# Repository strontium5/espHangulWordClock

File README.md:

# espHangulWordClock
esp8266 Hangul Word Clock

16x16 = 256 LEDs
2V@20mA
256*0.02 = 5.12A
5.12A*2V = 10.24W

5V@2A = 10W

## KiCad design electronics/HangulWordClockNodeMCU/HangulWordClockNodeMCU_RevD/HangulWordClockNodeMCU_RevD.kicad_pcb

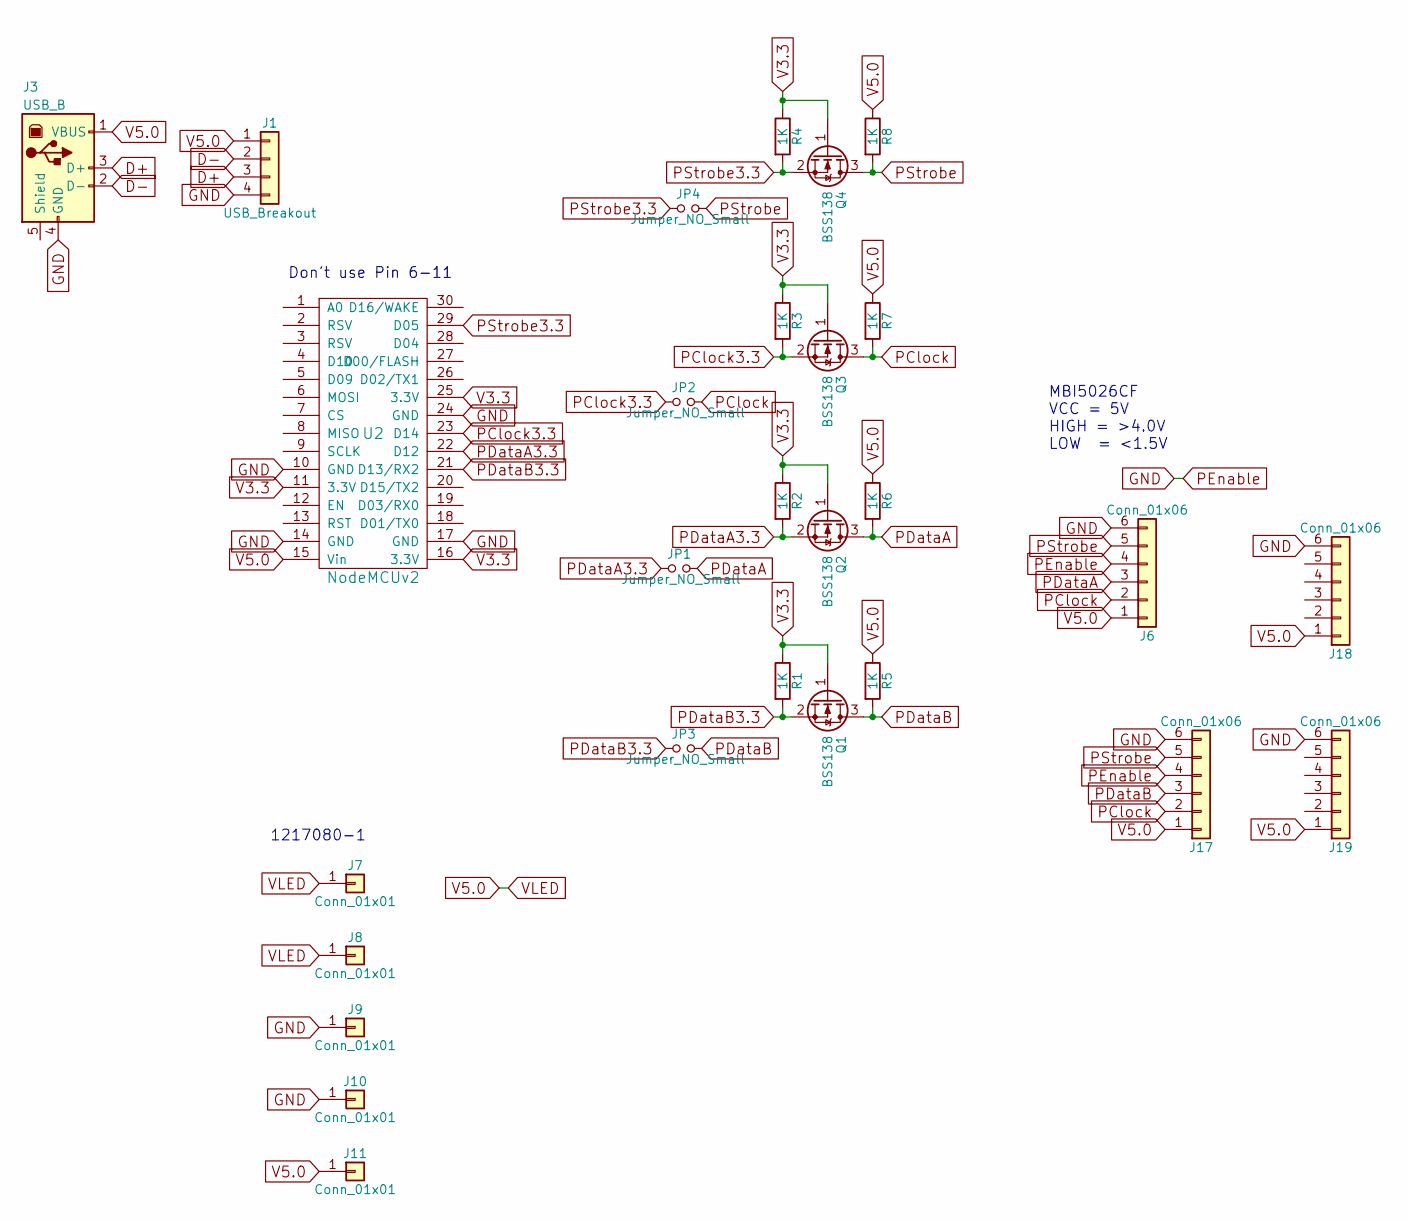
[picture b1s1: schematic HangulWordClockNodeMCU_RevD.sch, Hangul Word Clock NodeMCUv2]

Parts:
J1: USB_Breakout; Pin_Header_Straight_1x04
J3: USB_B
J6, J17, J18, J19: Conn_01x06; Socket_Strip_Straight_1x06
J7, J8, J9, J10, J11: Conn_01x01; 1217080-1
JP1, JP2, JP3, JP4: Jumper_NO_Small; GS2
Q1, Q2, Q3, Q4: BSS138; SOT-23
R1, R2, R3, R4, R5, R6, R7, R8: 1K; R_1206
U2: NodeMCUv2; NodeMCU_V1.0

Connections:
D+: J1.3, J3.3 (D+)
D-: J1.2, J3.2 (D-)
GND: J1.4, J3.4 (GND), J6.4, J6.6, J9.1, J10.1, J17.4, J17.6, J18.6, J19.6, U2.10 (GND), U2.14 (GND), U2.17 (GND), U2.24 (GND)
PClock: J6.2, J17.2, JP2.2, Q3.3 (D), R7.2
PClock3.3: JP2.1, Q3.2 (S), R3.2, U2.23 (D14)
PDataA: J6.3, JP1.2, Q2.3 (D), R6.2
PDataA3.3: JP1.1, Q2.2 (S), R2.2, U2.22 (D12)
PDataB: J17.3, JP3.2, Q1.3 (D), R5.2
PDataB3.3: JP3.1, Q1.2 (S), R1.2, U2.21 (D13/RX2)
PStrobe: J6.5, J17.5, JP4.2, Q4.3 (D), R8.2
PStrobe3.3: JP4.1, Q4.2 (S), R4.2, U2.29 (D05)
V3.3: Q1.1 (G), Q2.1 (G), Q3.1 (G), Q4.1 (G), R1.1, R2.1, R3.1, R4.1, U2.11 (3.3V), U2.16 (3.3V), U2.25 (3.3V)
V5.0: J1.1, J3.1 (VBUS), J6.1, J7.1, J8.1, J11.1, J17.1, J18.1, J19.1, R5.1, R6.1, R7.1, R8.1, U2.15 (Vin)

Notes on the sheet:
MBI5026CF VCC = 5V HIGH = >4.0V LOW = <1.5V
Don't use Pin 6-11
1217080-1

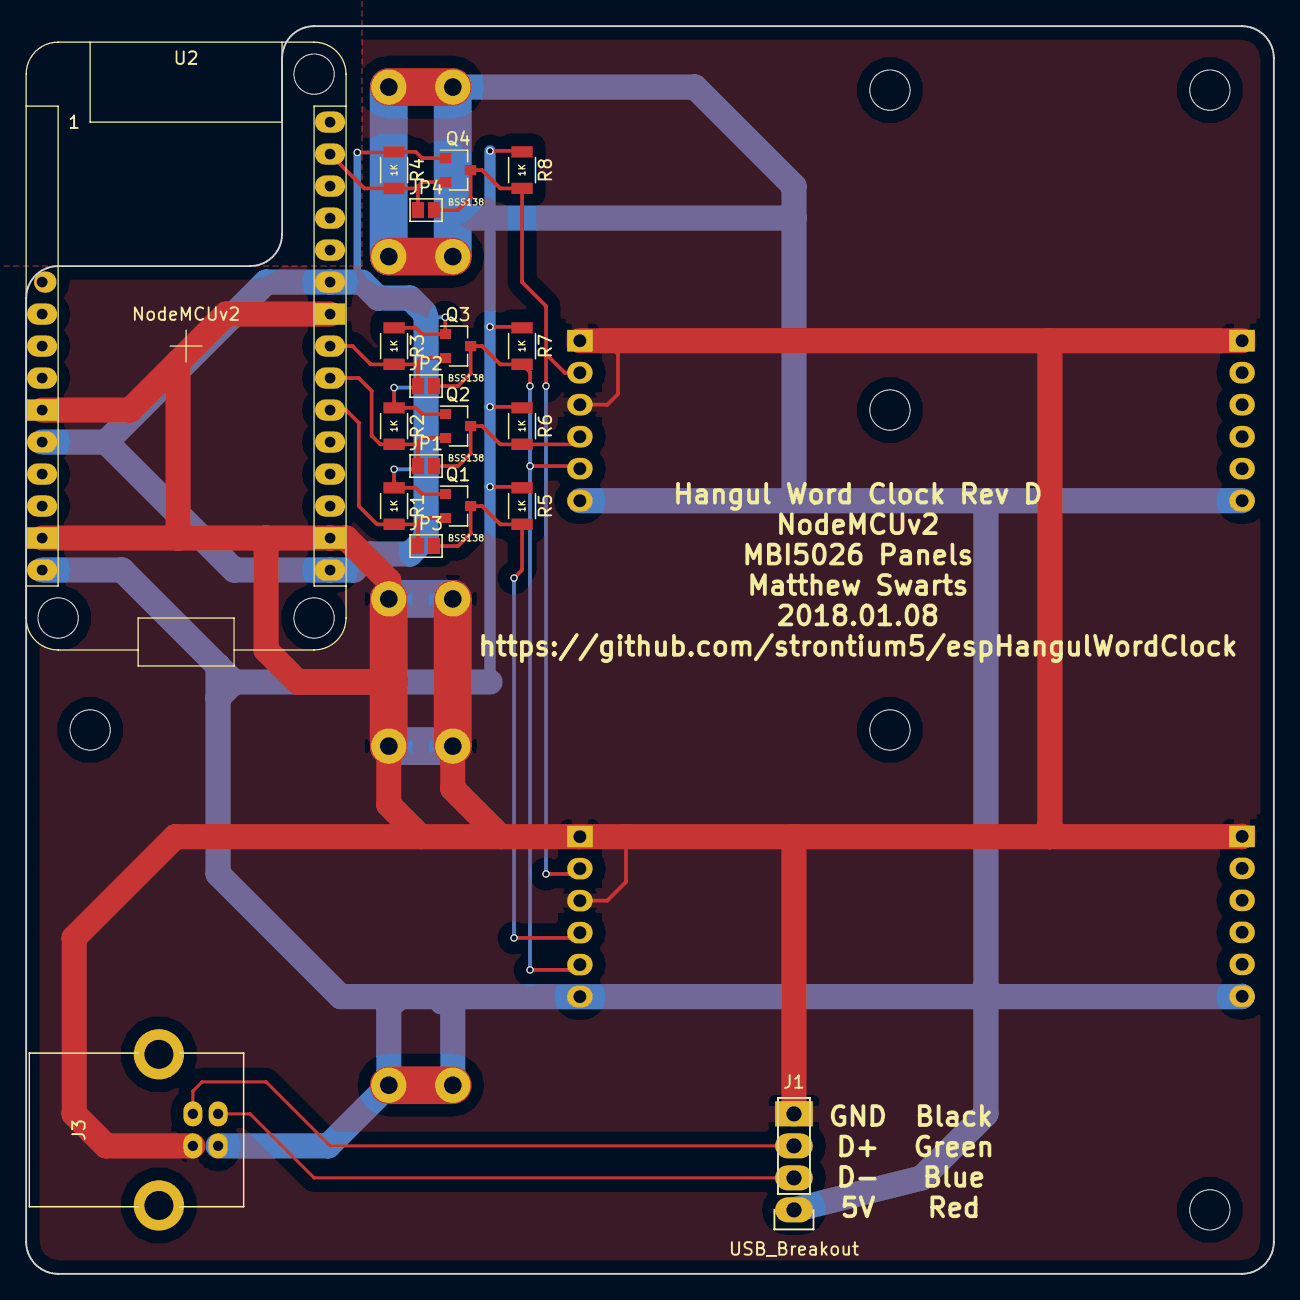
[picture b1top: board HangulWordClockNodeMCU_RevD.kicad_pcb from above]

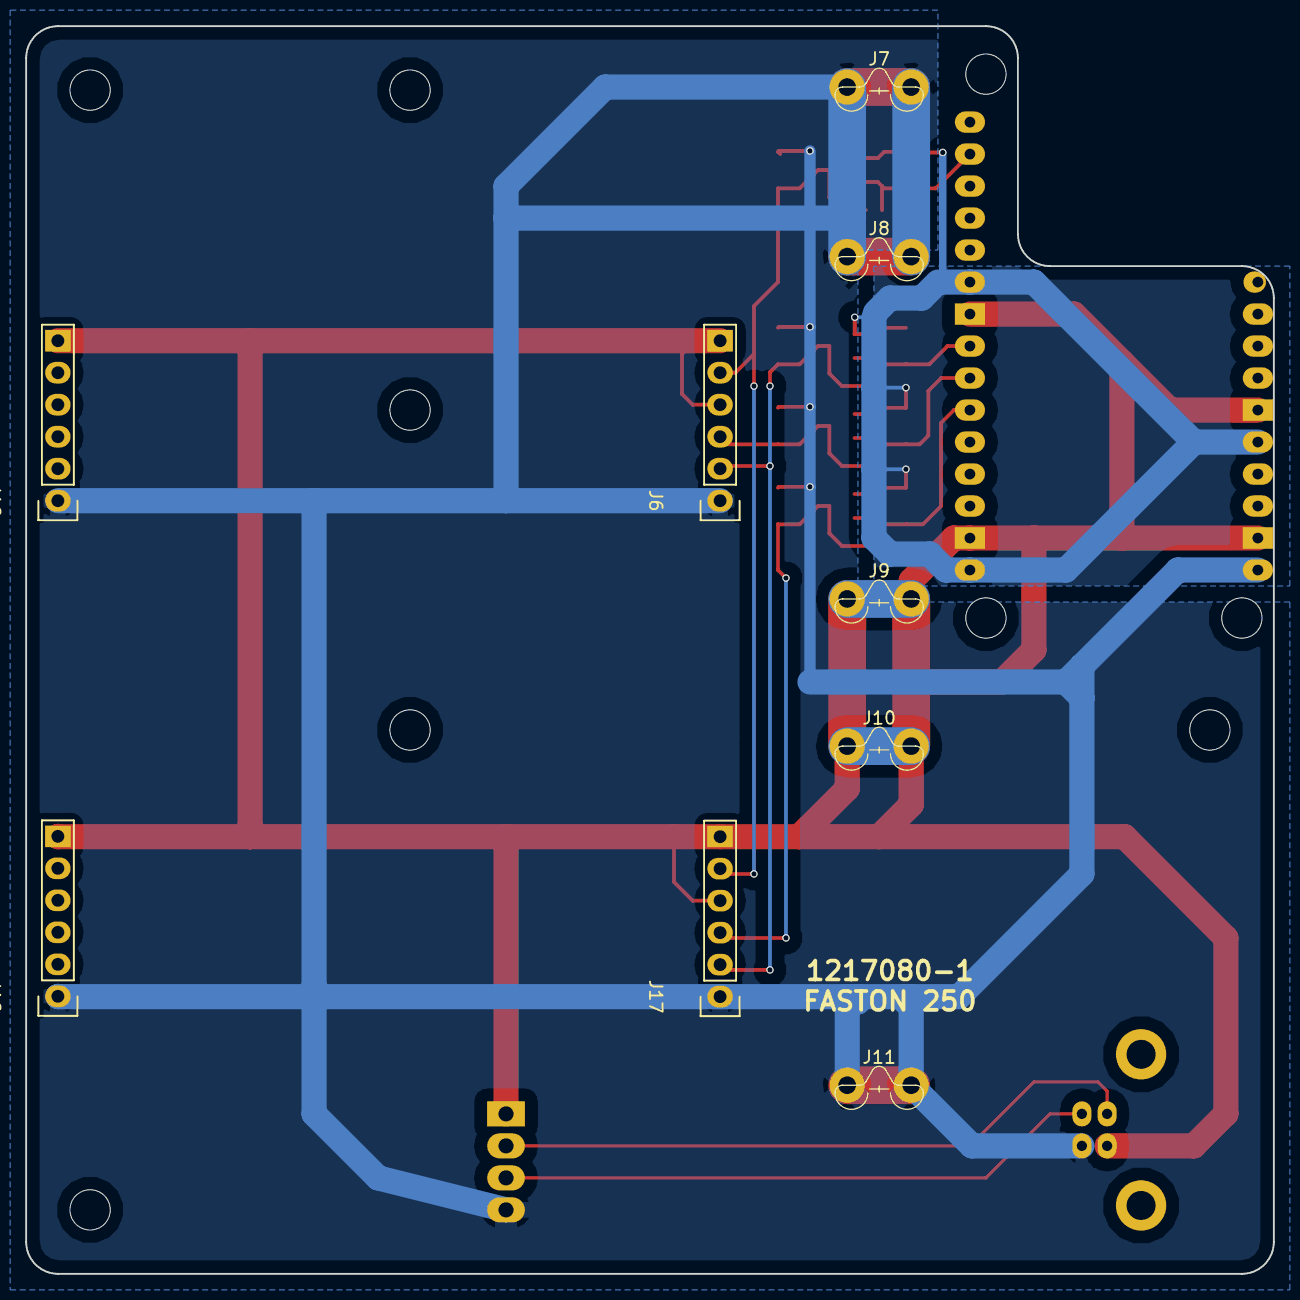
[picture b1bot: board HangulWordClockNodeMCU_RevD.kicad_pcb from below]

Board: 2 copper layers, 99.1 x 99.1 mm, 28 parts (9 on the bottom side), 13 nets.

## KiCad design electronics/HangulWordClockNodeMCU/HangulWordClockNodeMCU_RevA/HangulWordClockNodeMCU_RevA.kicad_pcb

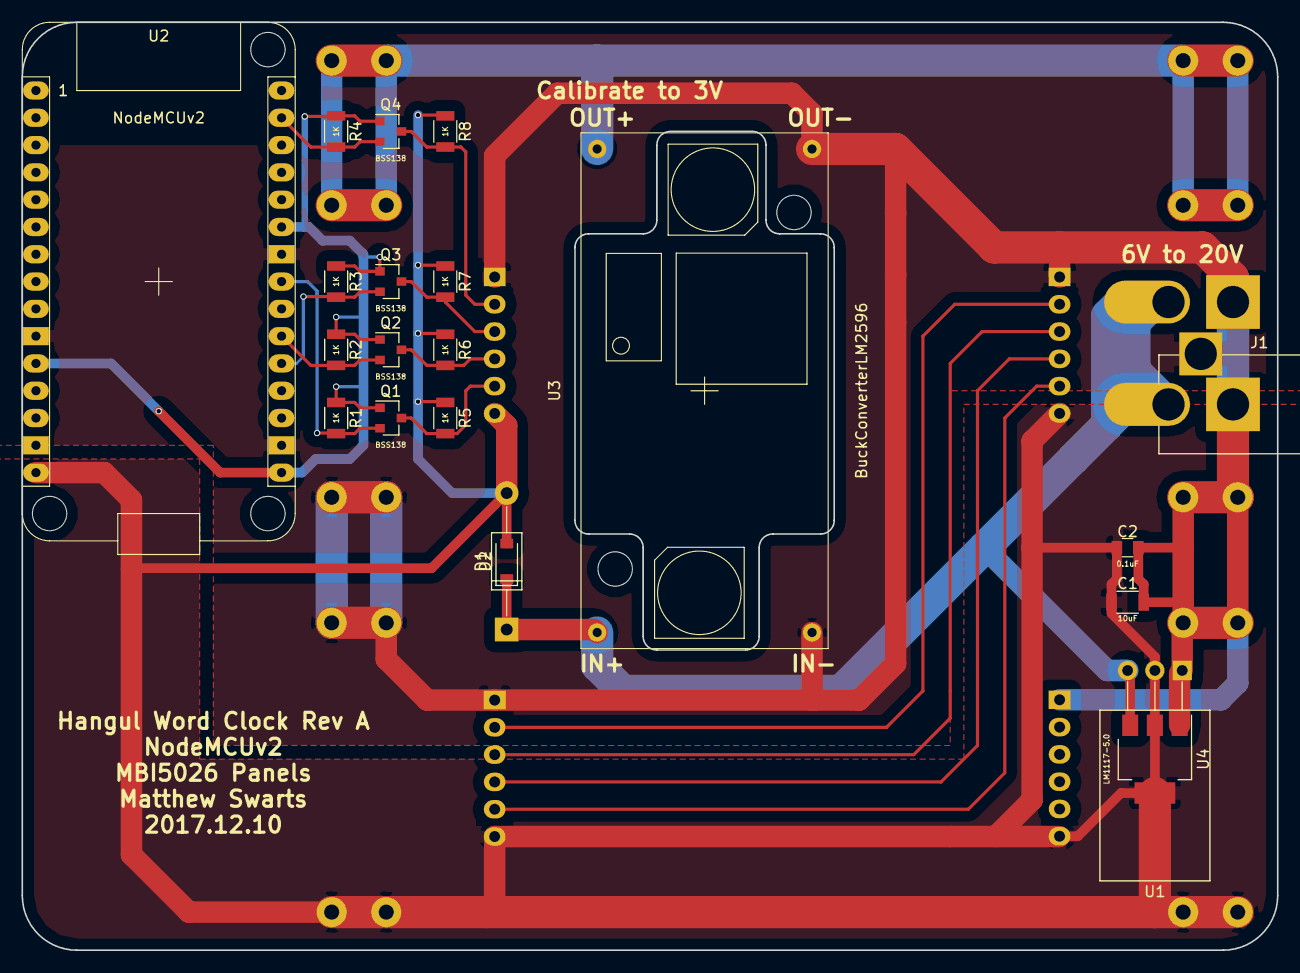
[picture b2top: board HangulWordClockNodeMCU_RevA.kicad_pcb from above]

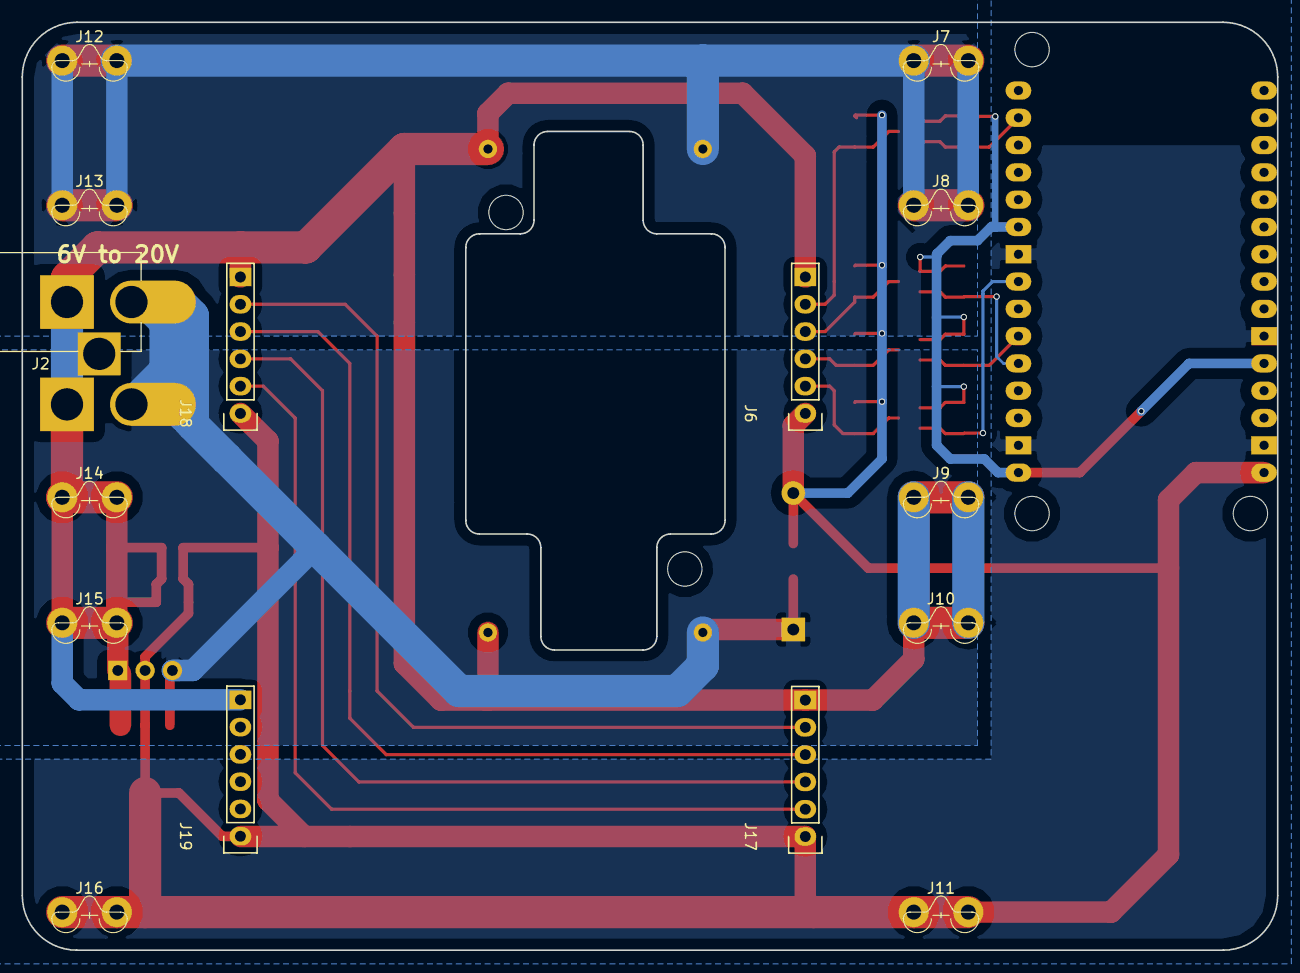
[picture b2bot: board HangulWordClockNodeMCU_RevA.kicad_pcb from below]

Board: 2 copper layers, 116.8 x 86.4 mm, 36 parts (15 on the bottom side), 17 nets.

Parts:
C1: 10uF; C_1206
C2: 0.1uF; C_0805
D1: D; D_DO-41_SOD81_P12.70mm_Horizontal
D2: D; D_SOD-123
J1, J2: Barrel_Jack; BARREL_JACK
J6, J17, J18, J19: Conn_01x06; Socket_Strip_Straight_1x06
J7, J8, J9, J10, J11, J12, J13, J14, J15, J16: Conn_01x01; 1217080-1
Q1, Q2, Q3, Q4: BSS138; SOT-23
R1, R2, R3, R4, R5, R6, R7, R8: 1K; R_1206
U1: LM1117-5.0; TO-220_Horizontal
U2: NodeMCUv2; NodeMCU_V1.0
U3: BuckConverterLM2596; LM2596Module
U4: LM1117-5.0; SOT-223-3Lead_TabPin2

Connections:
B: J17.2, J18.2
C: J17.3, J18.3
D: J17.4, J18.4
E: J17.5, J18.5
GND: C1.2, C2.2, J1.2, J1.3, J2.2, J6.6, J9.1, J10.1, J14.1, J15.1, J17.6, J18.6, J19.6, U1.1, U2.10, U2.14, U2.17, U2.24, U3.2, U3.3, U4.1
PClock: J6.2, Q1.3, R5.2
PClock3.3: Q1.2, R1.2, U2.23
PData: J6.3, Q2.3, R6.2
PData3.3: Q2.2, R2.2, U2.21
PEnable: J6.4, Q3.3, R7.2
PEnable3.3: Q3.2, R3.2, U2.20
PStrobe: J6.5, Q4.3, R8.2
PStrobe3.3: Q4.2, R4.2, U2.29
V3.3: Q1.1, Q2.1, Q3.1, Q4.1, R1.1, R2.1, R3.1, R4.1, U2.11, U2.16, U2.25
V5.0: C1.1, C2.1, D1.2, D2.2, J6.1, J11.1, J16.1, J17.1, J18.1, J19.1, R5.1, R6.1, R7.1, R8.1, U1.2, U2.15, U4.2
VLED: J7.1, J8.1, J12.1, J13.1, U3.4
Vin: D1.1, D2.1, J1.1, J2.1, U1.3, U3.1, U4.3

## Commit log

2017-12-10 added RevA electronics
2017-12-14 added RevB pcb
2017-12-14 added some 3d printed diffusers
2017-12-20 added scanes for 2596 module and beginning of correction to pcb design for a RevC; added masking bits for the display; wrote core display function
2017-12-21 added wifi configuration, ntp server connection, functions for drawings to the panel, functions to compute the masks for date or time, and functionality to update the time every second
2017-12-21 added Rev C which corrected the lm2956 module dimensions and adds jumpers for direct gpio control to bypass level shifters
2018-01-08 added Rev D for electronics, which only uses USB for power
